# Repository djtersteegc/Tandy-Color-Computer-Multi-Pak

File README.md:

Inspired by the work of [TheLittleEngineers](https://github.com/TheLittleEngineers/CoCoDragon-MultiPakInterface-CC-Multi-Pak_Version_1.2), this is my respin of the Tandy 26-3024 Multi-Pak (MPI).  It's targeted at the DIY builder so the schematic is pretty much straight out of the Tandy service manual with all THT parts, minus the power section (more on that later).  The board size has been reduced as much as possible, and I added two LED's to indicate power to the MPI and Coco to minimize accidental unplugging when still powered up.  The cart slots are numbered one to four, front to back, like a real MPI, but are rotated 90 degrees so the cart labels face forward.  This was mainly done to better suit devices like the Coco Fujinet that have indicator LED's on the top of the cart and I saw Ed has done the same with his MPI variants.

For power you have a couple of different options.  You can power directly via an external 5V PSU via either a barrel jack, USB-C, or MicroUSB ports.  Or you can use a 7.5V PSU into the barrel jack and a pair of AMS1117 5V VRM's will split the power load between slots 1/2 and 3/4.  For +12V and -12V there are solder jumpers on the back to take that from the Coco1 cartridge port, but no options to provide those voltages on a Coco2 or 3.

The case is a kickstand design to save on filament costs and printing time, but does have a 35mm tall top cover to better support the carts. There are also two different top designs, one that is mostly open from the cart slots to the board, and another that is fully shrouded, but uses almost double the filament.  I personally haven't printed the latter option yet.

Schematic - https://djtersteegc.github.io/Tandy-Color-Computer-Multi-Pak/Tandy%20Color%20Computer%20Multi-Pak%20Schematic.pdf

# BOM

CSV - https://djtersteegc.github.io/Tandy-Color-Computer-Multi-Pak/Tandy%20Color%20Computer%20Multi-Pak%20BOM.csv

iBOM - https://djtersteegc.github.io/Tandy-Color-Computer-Multi-Pak/ibom.html

Google Sheet with some AliExpress links - https://docs.google.com/spreadsheets/d/16bxERXJ9wRitJPs6XrFosqCZR3fNDdbd6zl7ltthO44/edit?usp=sharing

I tend the buy most everything from China, either AliExpress of UTSource (for logic). For power, first figure out how you want to power the board and then pick the correct optional parts.  I'm assuming everyone will install the barrel jack, either for direct 5V or to feed 7.5V into the VRM's.

# Switch

The original switches I ordered from AliExpress had a 5mm high handle that was 3mm thick. That same listing is now for a 4mm high handle model which is only 2mm thick. Looking at other listings, even the ones that still show the thicker handle appear to be sending out the shorter and thinner handled model based on review pictures posted.

There are now two STL's for the switch depending on which model you get.  **MPI Switch.stl** is for the original taller/thicker one, and **MPI Switch Small Handle.stl** for the shorter/thinner one.

# PCB Assembly

# GAL Programming

U8 is a standard GAL16V8.  The programming file is available in the [GAL](GAL) directory. This should be the [newer version](https://retrocomputing.stackexchange.com/questions/477/the-tandy-trs-80-multipack-interface-mpi) that is compatible with the Coco3, but I'm unable to verify since I only have 1's and 2's to test with currently.

# 3D Printing the Case

| Part                    | Filament |
| ----------------------- | -------- |
| MPI Top.stl             | 75g      |
| MPI Bottom.stl          | 62g      |
| MPI Cart Top.stl        | 20g      |
| MPI Foot.stl            | 12g      |
| MPI Switch.stl          | 1g       |
| MPI Top Full Shroud.stl | 137g     |

# Final Assembly

First screw the foot/kickstand to the bottom of the case with four [M3x10mm](https://www.aliexpress.us/item/2251832782301811.html) button head or countersunk head screws.

Then place the PCB, slide on the printed switch handle extender, place the cart top piece and then the larger top cover.  Flip over and assemble with eight M3x10mm to 14mm countersunk screws.

# Getting a Board to Build Your Own

Gerbers are available is you want to run your own batch. I would recommend ENIG (gold) finish since this is plugging into your cart edge connector. Otherwise if you are in the US hit my up on the Coco or FujiNet Discord (hideehoo is my username there) and if I have any extras I can drop one in the mail for $15 shipped.

# Versions

1.0 - Assembled and tested.  Initial batch of PCB's had produced had an incorrect switch footprint that required trimming of the locating tabs and the silkscreen with the slot numbering is reversed.  That has been corrected in the version 1.0 design files and gerbers in the intial upload to this repo.

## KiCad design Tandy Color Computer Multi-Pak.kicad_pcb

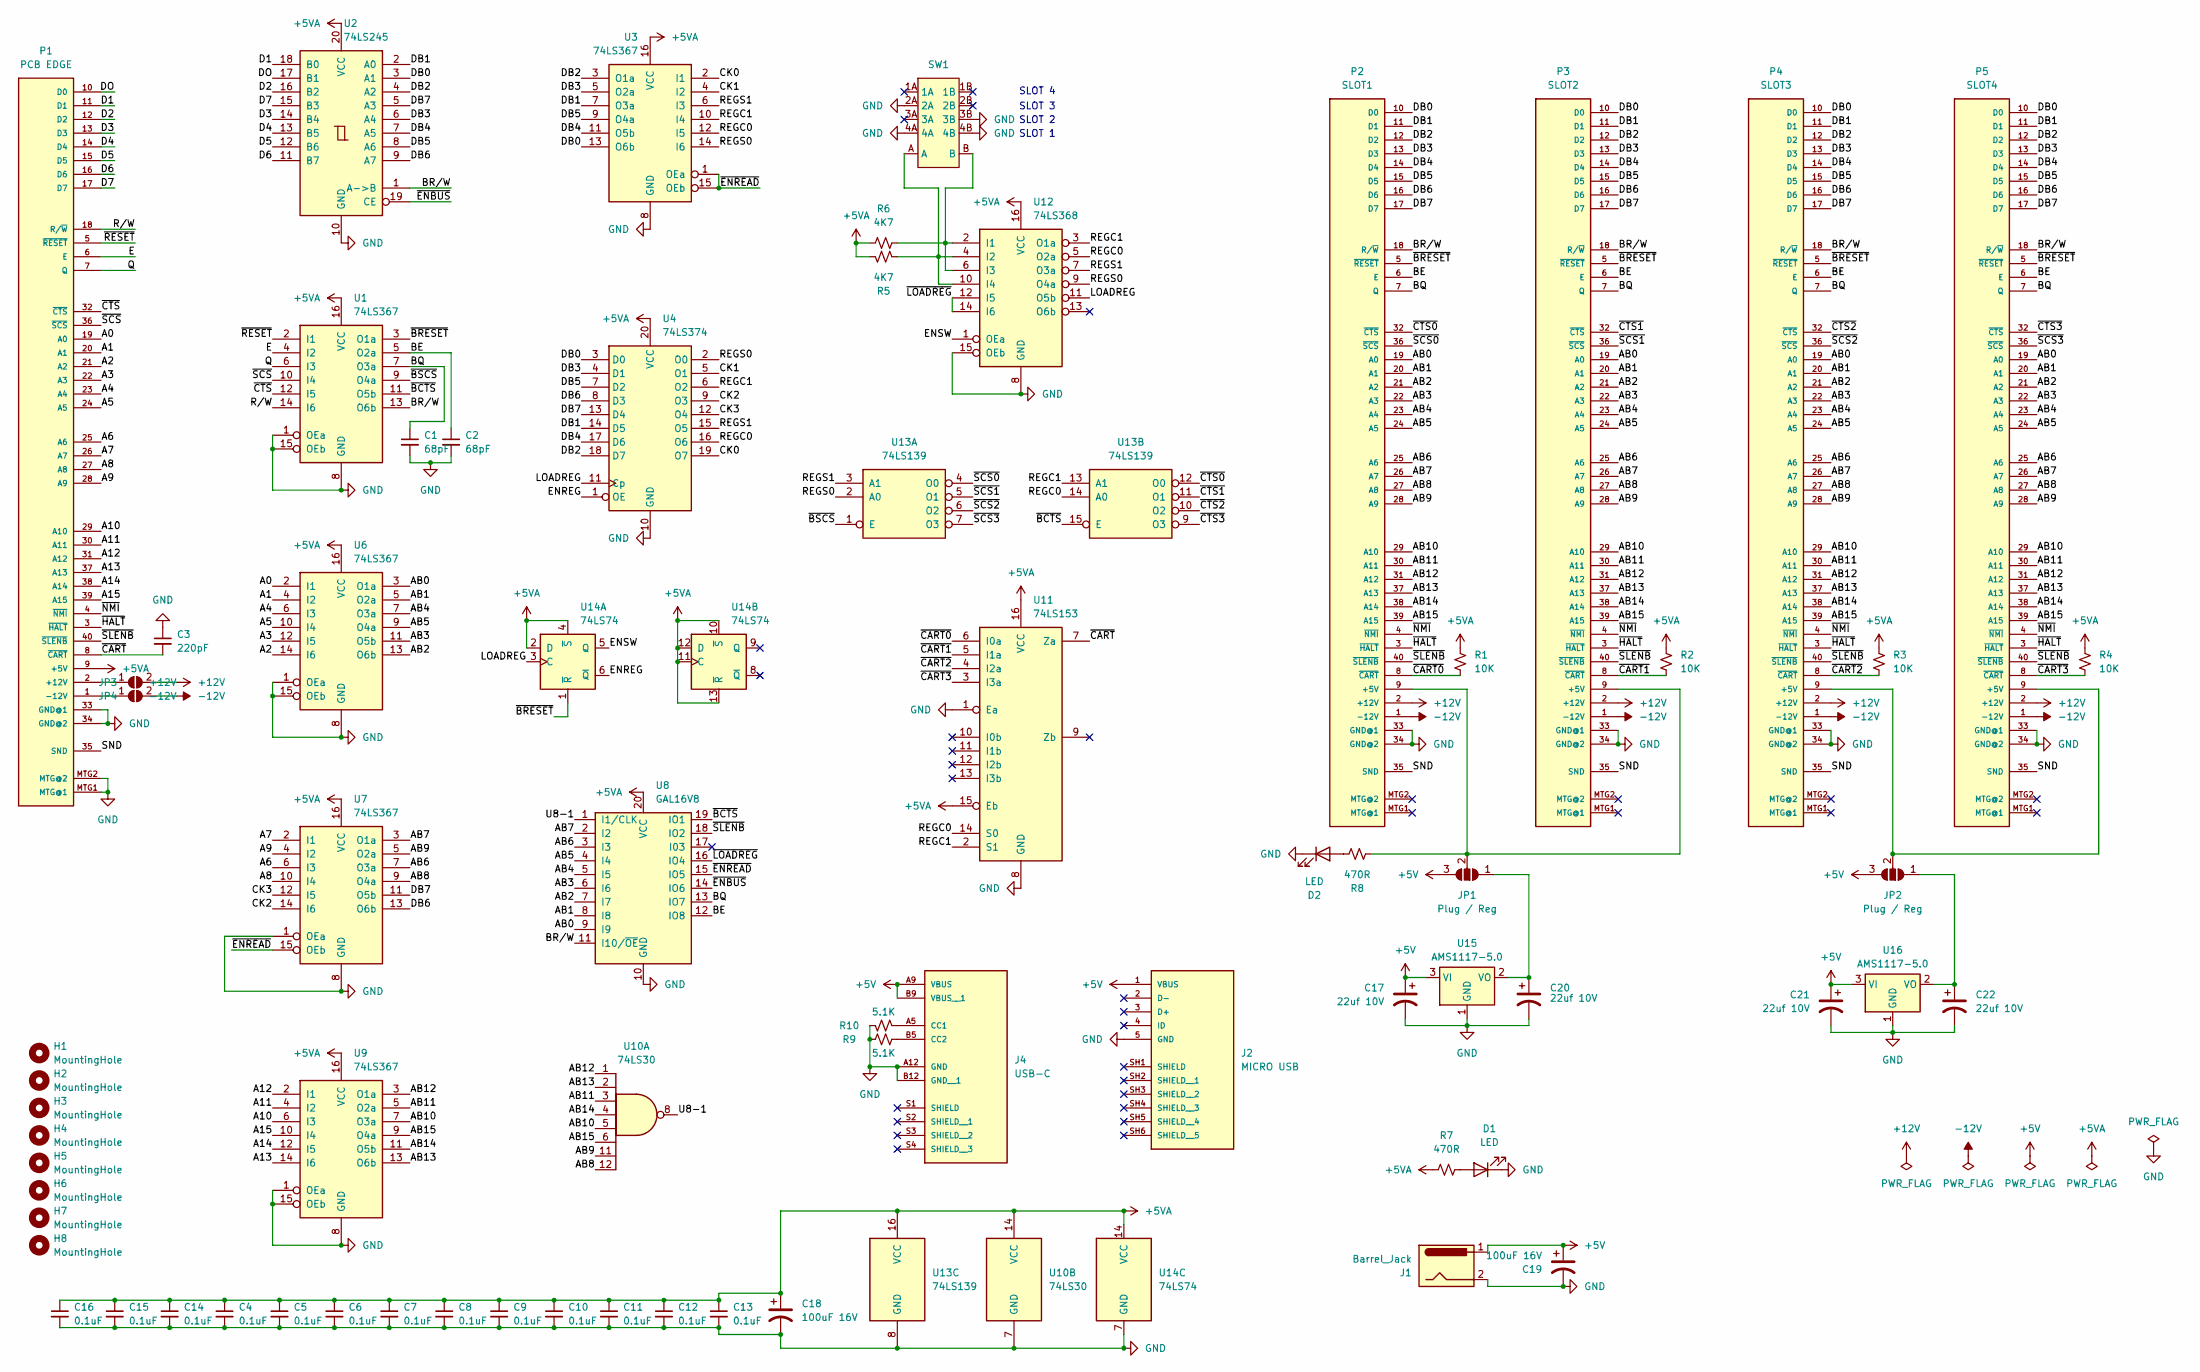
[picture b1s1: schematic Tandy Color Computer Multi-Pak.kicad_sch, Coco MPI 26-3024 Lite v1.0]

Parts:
C1, C2: 68pF; C_Disc_D4.7mm_W2.5mm_P5.00mm
C3: 220pF; C_Disc_D4.7mm_W2.5mm_P5.00mm
C4, C5, C6, C7, C8, C9, C10, C11, C12, C13, C14, C15, C16: 0.1uF; C_Disc_D4.7mm_W2.5mm_P5.00mm
C17, C20, C21, C22: 22uf 10V; CP_EIA-3528-12_Kemet-T_Pad1.50x2.35mm_HandSolder
C18, C19: 100uF 16V; CP_Radial_D6.3mm_P2.50mm
D1, D2: LED; LED_D3.0mm
H1, H2, H3, H4, H5, H6, H7, H8: MountingHole; MountingHole_3.2mm_M3
J1: Barrel_Jack; BarrelJack_Horizontal
J2: MICRO USB; SWITCHCRAFT_RAHMB20AUETR; PARTREV A
J4: USB-C; GCT_USB4125-GF-A_REVA2; PARTREV Rev A2
JP1, JP2: Plug / Reg; SolderJumper-3_P1.3mm_Open_Pad1.0x1.5mm_NumberLabels
JP3: +12V; SolderJumper-2_P1.3mm_Open_RoundedPad1.0x1.5mm
JP4: -12V; SolderJumper-2_P1.3mm_Open_RoundedPad1.0x1.5mm
P1: PCB EDGE; CoCo 40p PCB Cart Connector
P2: SLOT1; Coco 40p Cart Edge Connector
P3: SLOT2; Coco 40p Cart Edge Connector
P4: SLOT3; Coco 40p Cart Edge Connector
P5: SLOT4; Coco 40p Cart Edge Connector
R1, R2, R3, R4: 10K; R_Axial_DIN0207_L6.3mm_D2.5mm_P7.62mm_Horizontal
R5, R6: 4K7; R_Axial_DIN0207_L6.3mm_D2.5mm_P7.62mm_Horizontal
R7, R8: 470R; R_Axial_DIN0207_L6.3mm_D2.5mm_P7.62mm_Horizontal
R9, R10: 5.1K; R_Axial_DIN0204_L3.6mm_D1.6mm_P5.08mm_Horizontal
SW1: SK24D02VG4 2P4T Slide Switch
U1, U3, U6, U7, U9: 74LS367; DIP-16_W7.62mm_Socket
U2: 74LS245; DIP-20_W7.62mm_Socket
U4: 74LS374; DIP-20_W7.62mm_Socket
U8: GAL16V8; DIP-20_W7.62mm_Socket
U10: 74LS30; DIP-14_W7.62mm_Socket
U11: 74LS153; DIP-16_W7.62mm_Socket
U12: 74LS368; DIP-16_W7.62mm_Socket
U13: 74LS139; DIP-16_W7.62mm_Socket
U14: 74LS74; DIP-14_W7.62mm_Socket
U15, U16: AMS1117-5.0; SOT-223-3_TabPin2_Ext_Thermal

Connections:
+5V: C17.1, C19.1, C21.1, J1.1, J2.1 (VBUS), J4.A9 (VBUS), J4.B9 (VBUS__1), JP1.3 (B), JP2.3 (B), U15.3 (VI), U16.3 (VI)
+5VA: C4.1, C5.1, C6.1, C7.1, C8.1, C9.1, C10.1, C11.1, C12.1, C13.1, C14.1, C15.1, C16.1, C18.1, P1.9 (+5V), R1.1, R2.1, R3.1, R4.1, R5.1, R6.1, R7.1, U1.16 (VCC), U2.20 (VCC), U3.16 (VCC), U4.20 (VCC), U6.16 (VCC), U7.16 (VCC), U8.20 (VCC), U9.16 (VCC), U10.14 (VCC), U11.15 (Eb), U11.16 (VCC), U12.16 (VCC), U13.16 (VCC), U14.2 (D), U14.4 (~S), U14.10 (~S), U14.11 (C), U14.12 (D), U14.13 (~R), U14.14 (VCC)
+12V: JP3.2 (B), P2.2 (+12V), P3.2 (+12V), P4.2 (+12V), P5.2 (+12V)
-12V: JP4.2 (B), P2.1 (-12V), P3.1 (-12V), P4.1 (-12V), P5.1 (-12V)
/A0: P1.19 (A0), U6.2 (I1)
/A1: P1.20 (A1), U6.4 (I2)
/A2: P1.21 (A2), U6.14 (I6)
/A3: P1.22 (A3), U6.12 (I5)
/A4: P1.23 (A4), U6.6 (I3)
/A5: P1.24 (A5), U6.10 (I4)
/A6: P1.25 (A6), U7.6 (I3)
/A7: P1.26 (A7), U7.2 (I1)
/A8: P1.27 (A8), U7.10 (I4)
/A9: P1.28 (A9), U7.4 (I2)
/A10: P1.29 (A10), U9.6 (I3)
/A11: P1.30 (A11), U9.4 (I2)
/A12: P1.31 (A12), U9.2 (I1)
/A13: P1.37 (A13), U9.14 (I6)
/A14: P1.38 (A14), U9.12 (I5)
/A15: P1.39 (A15), U9.10 (I4)
/AB0: P2.19 (A0), P3.19 (A0), P4.19 (A0), P5.19 (A0), U6.3 (O1a), U8.9 (I9)
/AB1: P2.20 (A1), P3.20 (A1), P4.20 (A1), P5.20 (A1), U6.5 (O2a), U8.8 (I8)
/AB2: P2.21 (A2), P3.21 (A2), P4.21 (A2), P5.21 (A2), U6.13 (O6b), U8.7 (I7)
/AB3: P2.22 (A3), P3.22 (A3), P4.22 (A3), P5.22 (A3), U6.11 (O5b), U8.6 (I6)
/AB4: P2.23 (A4), P3.23 (A4), P4.23 (A4), P5.23 (A4), U6.7 (O3a), U8.5 (I5)
/AB5: P2.24 (A5), P3.24 (A5), P4.24 (A5), P5.24 (A5), U6.9 (O4a), U8.4 (I4)
/AB6: P2.25 (A6), P3.25 (A6), P4.25 (A6), P5.25 (A6), U7.7 (O3a), U8.3 (I3)
/AB7: P2.26 (A7), P3.26 (A7), P4.26 (A7), P5.26 (A7), U7.3 (O1a), U8.2 (I2)
/AB8: P2.27 (A8), P3.27 (A8), P4.27 (A8), P5.27 (A8), U7.9 (O4a), U10.12
/AB9: P2.28 (A9), P3.28 (A9), P4.28 (A9), P5.28 (A9), U7.5 (O2a), U10.11
/AB10: P2.29 (A10), P3.29 (A10), P4.29 (A10), P5.29 (A10), U9.7 (O3a), U10.5
/AB11: P2.30 (A11), P3.30 (A11), P4.30 (A11), P5.30 (A11), U9.5 (O2a), U10.3
/AB12: P2.31 (A12), P3.31 (A12), P4.31 (A12), P5.31 (A12), U9.3 (O1a), U10.1
/AB13: P2.37 (A13), P3.37 (A13), P4.37 (A13), P5.37 (A13), U9.13 (O6b), U10.2
/AB14: P2.38 (A14), P3.38 (A14), P4.38 (A14), P5.38 (A14), U9.11 (O5b), U10.4
/AB15: P2.39 (A15), P3.39 (A15), P4.39 (A15), P5.39 (A15), U9.9 (O4a), U10.6
/BE: C2.1, P2.6 (E), P3.6 (E), P4.6 (E), P5.6 (E), U1.5 (O2a), U8.12 (IO8)
/BQ: C1.1, P2.7 (Q), P3.7 (Q), P4.7 (Q), P5.7 (Q), U1.7 (O3a), U8.13 (IO7)
/BR/W: P2.18 (R/~W), P3.18 (R/~W), P4.18 (R/~W), P5.18 (R/~W), U1.13 (O6b), U2.1 (A->B), U8.11 (I10/~OE)
/CK0: U3.2 (I1), U4.19 (O7)
/CK1: U3.4 (I2), U4.5 (O1)
/CK2: U4.9 (O3), U7.14 (I6)
/CK3: U4.12 (O4), U7.12 (I5)
/D1: P1.11 (D1), U2.18 (B0)
/D2: P1.12 (D2), U2.16 (B2)
/D3: P1.13 (D3), U2.14 (B4)
/D4: P1.14 (D4), U2.13 (B5)
/D5: P1.15 (D5), U2.12 (B6)
/D6: P1.16 (D6), U2.11 (B7)
/D7: P1.17 (D7), U2.15 (B3)
/DB0: P2.10 (D0), P3.10 (D0), P4.10 (D0), P5.10 (D0), U2.3 (A1), U3.13 (O6b), U4.3 (D0)
/DB1: P2.11 (D1), P3.11 (D1), P4.11 (D1), P5.11 (D1), U2.2 (A0), U3.7 (O3a), U4.14 (D5)
/DB2: P2.12 (D2), P3.12 (D2), P4.12 (D2), P5.12 (D2), U2.4 (A2), U3.3 (O1a), U4.18 (D7)
/DB3: P2.13 (D3), P3.13 (D3), P4.13 (D3), P5.13 (D3), U2.6 (A4), U3.5 (O2a), U4.4 (D1)
/DB4: P2.14 (D4), P3.14 (D4), P4.14 (D4), P5.14 (D4), U2.7 (A5), U3.11 (O5b), U4.17 (D6)
/DB5: P2.15 (D5), P3.15 (D5), P4.15 (D5), P5.15 (D5), U2.8 (A6), U3.9 (O4a), U4.7 (D2)
/DB6: P2.16 (D6), P3.16 (D6), P4.16 (D6), P5.16 (D6), U2.9 (A7), U4.8 (D3), U7.13 (O6b)
/DB7: P2.17 (D7), P3.17 (D7), P4.17 (D7), P5.17 (D7), U2.5 (A3), U4.13 (D4), U7.11 (O5b)
/DO: P1.10 (D0), U2.17 (B1)
/E: P1.6 (E), U1.4 (I2)
/ENREG: U4.1 (OE), U14.6 (~Q)
/ENSW: U12.1 (OEa), U14.5 (Q)
/LOADREG: U4.11 (Cp), U12.11 (O5b), U14.3 (C)
/Q: P1.7 (Q), U1.6 (I3)
/REGC0: U3.12 (I5), U4.16 (O6), U11.14 (S0), U12.5 (O2a), U13.14 (A0)
/REGC1: U3.10 (I4), U4.6 (O2), U11.2 (S1), U12.3 (O1a), U13.13 (A1)
/REGS0: U3.14 (I6), U4.2 (O0), U12.9 (O4a), U13.2 (A0)
/REGS1: U3.6 (I3), U4.15 (O5), U12.7 (O3a), U13.3 (A1)
/R/W: P1.18 (R/~W), U1.14 (I6)
/SND: P1.35 (SND), P2.35 (SND), P3.35 (SND), P4.35 (SND), P5.35 (SND)
/U8-1: U8.1 (I1/CLK), U10.8
/~BCTS: U1.11 (O5b), U8.19 (IO1), U13.15 (E)
/~BRESET: P2.5 (~RESET), P3.5 (~RESET), P4.5 (~RESET), P5.5 (~RESET), U1.3 (O1a), U14.1 (~R)
/~BSCS: U1.9 (O4a), U13.1 (E)
/~CART0: P2.8 (~CART), R1.2, U11.6 (I0a)
/~CART1: P3.8 (~CART), R2.2, U11.5 (I1a)
/~CART2: P4.8 (~CART), R3.2, U11.4 (I2a)
/~CART3: P5.8 (~CART), R4.2, U11.3 (I3a)
/~CART: C3.2, P1.8 (~CART), U11.7 (Za)
/~CTS0: P2.32 (~CTS), U13.12 (O0)
/~CTS1: P3.32 (~CTS), U13.11 (O1)
/~CTS2: P4.32 (~CTS), U13.10 (O2)
/~CTS3: P5.32 (~CTS), U13.9 (O3)
/~CTS: P1.32 (~CTS), U1.12 (I5)
/~ENBUS: U2.19 (CE), U8.14 (IO6)
/~ENREAD: U3.1 (OEa), U3.15 (OEb), U7.15 (OEb), U8.15 (IO5)
/~HALT: P1.3 (~HALT), P2.3 (~HALT), P3.3 (~HALT), P4.3 (~HALT), P5.3 (~HALT)
/~LOADREG: U8.16 (IO4), U12.12 (I5), U12.14 (I6)
/~NMI: P1.4 (~NMI), P2.4 (~NMI), P3.4 (~NMI), P4.4 (~NMI), P5.4 (~NMI)
/~RESET: P1.5 (~RESET), U1.2 (I1)
/~SCS0: P2.36 (~SCS), U13.4 (O0)
/~SCS1: P3.36 (~SCS), U13.5 (O1)
/~SCS2: P4.36 (~SCS), U13.6 (O2)
/~SCS3: P5.36 (~SCS), U13.7 (O3)
/~SCS: P1.36 (~SCS), U1.10 (I4)
/~SLENB: P1.40 (~SLENB), P2.40 (~SLENB), P3.40 (~SLENB), P4.40 (~SLENB), P5.40 (~SLENB), U8.18 (IO2)
GND: C1.2, C2.2, C3.1, C4.2, C5.2, C6.2, C7.2, C8.2, C9.2, C10.2, C11.2, C12.2, C13.2, C14.2, C15.2, C16.2, C17.2, C18.2, C19.2, C20.2, C21.2, C22.2, D1.1 (K), D2.1 (K), J1.2, J2.5 (GND), J4.A12 (GND), J4.B12 (GND__1), P1.33 (GND@1), P1.34 (GND@2), P1.MTG1 (MTG@1), P1.MTG2 (MTG@2), P2.33 (GND@1), P2.34 (GND@2), P3.33 (GND@1), P3.34 (GND@2), P4.33 (GND@1), P4.34 (GND@2), P5.33 (GND@1), P5.34 (GND@2), R9.2, R10.2, SW1.2A, SW1.3B, SW1.4A, SW1.4B, U1.1 (OEa), U1.8 (GND), U1.15 (OEb), U2.10 (GND), U3.8 (GND), U4.10 (GND), U6.1 (OEa), U6.8 (GND), U6.15 (OEb), U7.1 (OEa), U7.8 (GND), U8.10 (GND), U9.1 (OEa), U9.8 (GND), U9.15 (OEb), U10.7 (GND), U11.1 (Ea), U11.8 (GND), U12.8 (GND), U12.15 (OEb), U13.8 (GND), U14.7 (GND), U15.1 (GND), U16.1 (GND)
unnamed: D1.2 (A), R7.2
unnamed: D2.2 (A), R8.2
unnamed: J4.A5 (CC1), R10.1
unnamed: J4.B5 (CC2), R9.1
unnamed: C20.1, JP1.1 (A), U15.2 (VO)
unnamed: JP1.2 (C), P2.9 (+5V), P3.9 (+5V), R8.1
unnamed: C22.1, JP2.1 (A), U16.2 (VO)
unnamed: JP2.2 (C), P4.9 (+5V), P5.9 (+5V)
unnamed: JP3.1 (A), P1.2 (+12V)
unnamed: JP4.1 (A), P1.1 (-12V)
unnamed: R6.2, SW1.B, U12.2 (I1), U12.6 (I3)
unnamed: R5.2, SW1.A, U12.4 (I2), U12.10 (I4)

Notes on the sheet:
SLOT 3
SLOT 4
SLOT 2
SLOT 1

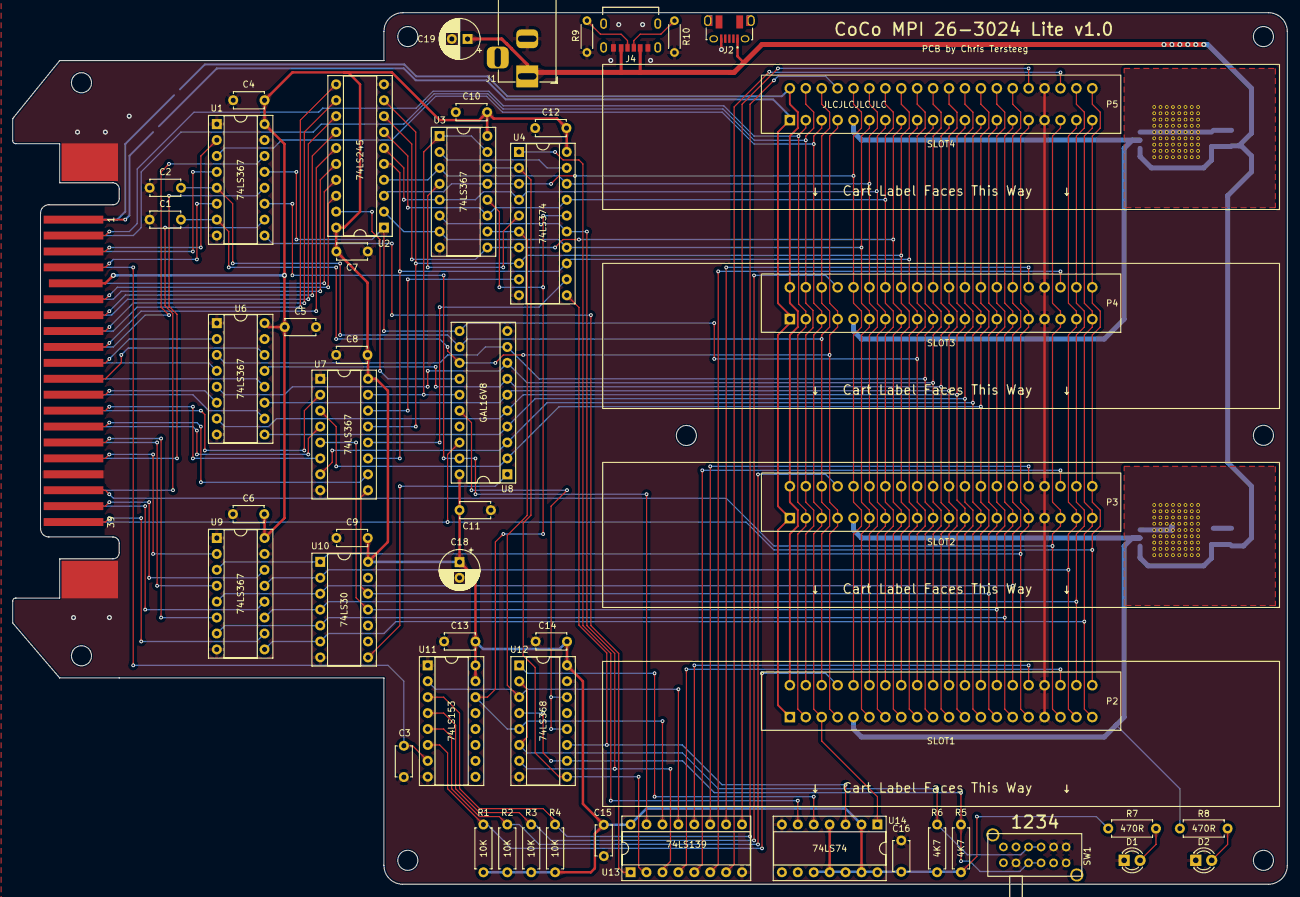
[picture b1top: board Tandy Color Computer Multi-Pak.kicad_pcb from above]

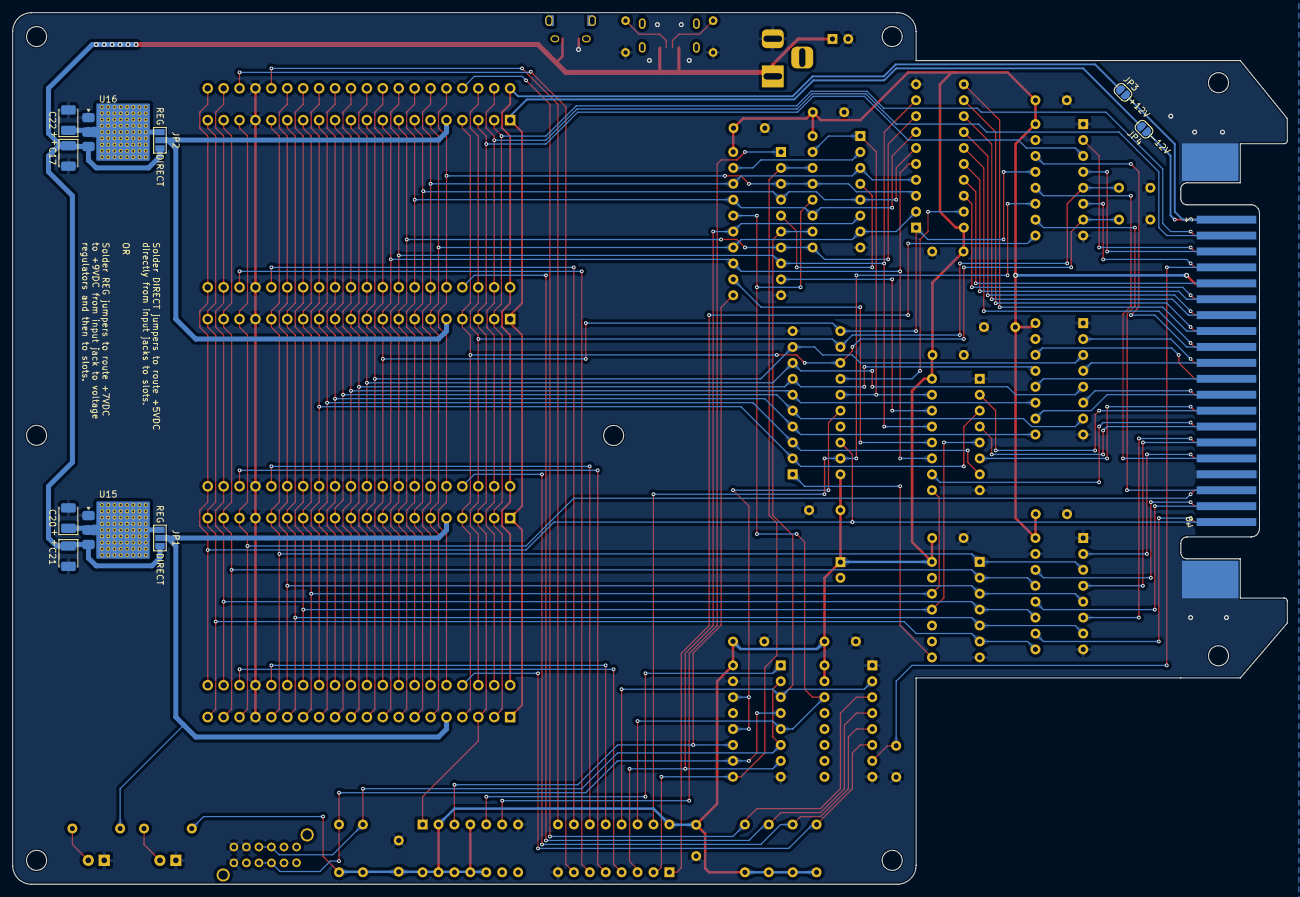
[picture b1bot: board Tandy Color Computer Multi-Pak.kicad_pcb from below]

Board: 2 copper layers, 203.4 x 139.1 mm, 70 parts (10 on the bottom side), 109 nets.

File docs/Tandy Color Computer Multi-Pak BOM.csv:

"Reference","Value","Datasheet","Footprint","Qty","DNP"
"C1,C2","68pF","~","Capacitor_THT:C_Disc_D4.7mm_W2.5mm_P5.00mm","2",""
"C3","220pF","~","Capacitor_THT:C_Disc_D4.7mm_W2.5mm_P5.00mm","1",""
"C4,C5,C6,C7,C8,C9,C10,C11,C12,C13,C14,C15,C16","0.1uF","~","Capacitor_THT:C_Disc_D4.7mm_W2.5mm_P5.00mm","13",""
"C17,C20,C21,C22","22uf 10V","~","Capacitor_Tantalum_SMD:CP_EIA-3528-12_Kemet-T_Pad1.50x2.35mm_HandSolder","4",""
"C18,C19","100uF 16V","~","Capacitor_THT:CP_Radial_D6.3mm_P2.50mm","2",""
"D1,D2","LED","~","LED_THT:LED_D3.0mm","2",""
"H1,H2,H3,H4,H5,H6,H7,H8","MountingHole","~","MountingHole:MountingHole_3.2mm_M3","8",""
"J1","Barrel_Jack","~","Connector_BarrelJack:BarrelJack_Horizontal","1",""
"J2","MICRO USB","~","RAHMB20AUETR:SWITCHCRAFT_RAHMB20AUETR","1",""
"J4","USB-C","","USB4125_GF_A:GCT_USB4125-GF-A_REVA2","1",""
"JP1,JP2","Plug / Reg","~","Jumper:SolderJumper-3_P1.3mm_Open_Pad1.0x1.5mm_NumberLabels","2",""
"JP3","+12V","~","Jumper:SolderJumper-2_P1.3mm_Open_RoundedPad1.0x1.5mm","1",""
"JP4","-12V","~","Jumper:SolderJumper-2_P1.3mm_Open_RoundedPad1.0x1.5mm","1",""
"P1","PCB EDGE","","Tersteeg:CoCo 40p PCB Cart Connector","1",""
"P2","SLOT1","","Tersteeg:Coco 40p Cart Edge Connector","1",""
"P3","SLOT2","","Tersteeg:Coco 40p Cart Edge Connector","1",""
"P4","SLOT3","","Tersteeg:Coco 40p Cart Edge Connector","1",""
"P5","SLOT4","","Tersteeg:Coco 40p Cart Edge Connector","1",""
"R1,R2,R3,R4","10K","~","Resistor_THT:R_Axial_DIN0207_L6.3mm_D2.5mm_P7.62mm_Horizontal","4",""
"R5,R6","4K7","~","Resistor_THT:R_Axial_DIN0207_L6.3mm_D2.5mm_P7.62mm_Horizontal","2",""
"R7,R8","470R","~","Resistor_THT:R_Axial_DIN0207_L6.3mm_D2.5mm_P7.62mm_Horizontal","2",""
"R9,R10","5.1K","~","Resistor_THT:R_Axial_DIN0204_L3.6mm_D1.6mm_P5.08mm_Horizontal","2",""
"SW1","~","","Tersteeg:SK24D02VG4 2P4T Slide Switch","1",""
"U1,U3,U6,U7,U9","74LS367","http://www.ti.com/lit/gpn/sn74LS367","Package_DIP:DIP-16_W7.62mm_Socket","5",""
"U2","74LS245","http://www.ti.com/lit/gpn/sn74LS245","Package_DIP:DIP-20_W7.62mm_Socket","1",""
"U4","74LS374","http://www.ti.com/lit/gpn/sn74LS374","Package_DIP:DIP-20_W7.62mm_Socket","1",""
"U8","GAL16V8","","Package_DIP:DIP-20_W7.62mm_Socket","1",""
"U10","74LS30","http://www.ti.com/lit/gpn/sn74LS30","Package_DIP:DIP-14_W7.62mm_Socket","1",""
"U11","74LS153","http://www.ti.com/lit/gpn/sn74LS153","Package_DIP:DIP-16_W7.62mm_Socket","1",""
"U12","74LS368","http://www.ti.com/lit/gpn/sn74LS368","Package_DIP:DIP-16_W7.62mm_Socket","1",""
"U13","74LS139","http://www.ti.com/lit/ds/symlink/sn74ls139a.pdf","Package_DIP:DIP-16_W7.62mm_Socket","1",""
"U14","74LS74","74xx/74hc_hct74.pdf","Package_DIP:DIP-14_W7.62mm_Socket","1",""
"U15,U16","AMS1117-5.0","http://www.advanced-monolithic.com/pdf/ds1117.pdf","Tersteeg:SOT-223-3_TabPin2_Ext_Thermal","2",""

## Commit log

2024-06-11 Initial 1.0 version
2024-06-11 Fix links
2024-09-14 Add programming file for the GAL
2026-01-24 Update docs for assembly, add alternative switch model
2026-01-24 Add info on GAL programming
